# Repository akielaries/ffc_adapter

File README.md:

# FFC adapter board
This is a custom PCB to interface the FFC pins of the Tang Mega 138k and Tang Mega 60k FPGAs

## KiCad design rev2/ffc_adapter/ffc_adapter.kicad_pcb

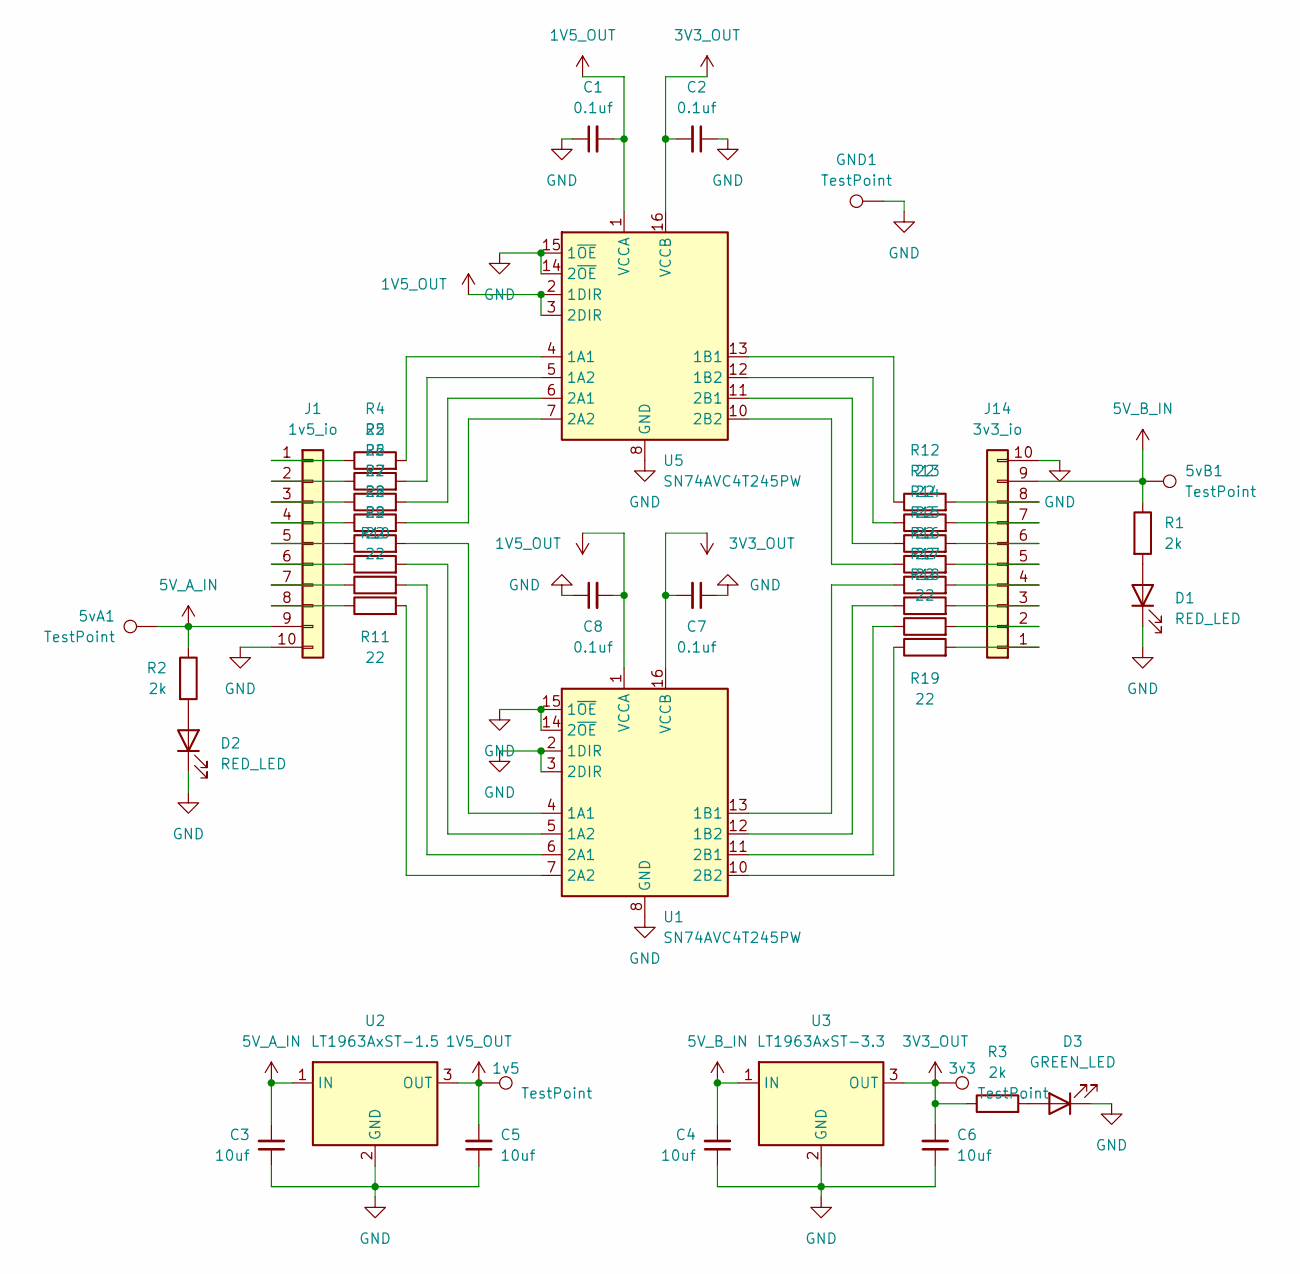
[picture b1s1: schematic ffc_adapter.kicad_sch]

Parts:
1v5, 3v3, 5vA1, 5vB1: TestPoint; TestPoint_Pad_D1.0mm
C1, C2, C7, C8: 0.1uf; C_0805_2012Metric
C3, C4, C5, C6: 10uf; C_0805_2012Metric
D1, D2: RED_LED; LED_0603_1608Metric
D3: GREEN_LED; LED_0603_1608Metric
GND1: TestPoint; TestPoint_Pad_D1.0mm
J1: 1v5_io; Hirose_FH12-10S-0.5SH_1x10-1MP_P0.50mm_Horizontal
J14: 3v3_io; Hirose_FH12-10S-0.5SH_1x10-1MP_P0.50mm_Horizontal
R1, R2, R3: 2k; R_0201_0603Metric; DigiKey_Part_Number 311-10.0KCRCT-ND
R4, R5, R6, R7, R8, R9, R10, R11, R12, R13, R14, R15, R16, R17, R18, R19: 22; R_0201_0603Metric; DigiKey_Part_Number 311-10.0KCRCT-ND
U1, U5: SN74AVC4T245PW; TSSOP-16_4.4x5mm_P0.65mm
U2: LT1963AxST-1.5; SOT-223-3_TabPin2
U3: LT1963AxST-3.3; SOT-223-3_TabPin2

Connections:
1V5_OUT: 1v5.1, C1.2, C5.2, C8.2, U1.1 (VCCA), U2.3 (OUT), U5.1 (VCCA), U5.2 (1DIR), U5.3 (2DIR)
3V3_OUT: 3v3.1, C2.2, C6.2, C7.2, R3.1, U1.16 (VCCB), U3.3 (OUT), U5.16 (VCCB)
5V_A_IN: 5vA1.1, C3.2, J1.9, R2.1, U2.1 (IN)
5V_B_IN: 5vB1.1, C4.2, J14.9, R1.1, U3.1 (IN)
GND: C1.1, C2.1, C3.1, C4.1, C5.1, C6.1, C7.1, C8.1, D1.1 (K), D2.1 (K), D3.1 (K), GND1.1, J1.10, J14.10, U1.2 (1DIR), U1.3 (2DIR), U1.8 (GND), U1.9 (GND), U1.14 (2~OE), U1.15 (1~OE), U2.2 (GND), U3.2 (GND), U5.8 (GND), U5.9 (GND), U5.14 (2~OE), U5.15 (1~OE)
unnamed: D1.2 (A), R1.2
unnamed: D2.2 (A), R2.2
unnamed: D3.2 (A), R3.2
unnamed: J1.1, R4.1
unnamed: J1.2, R5.1
unnamed: J1.3, R6.1
unnamed: J1.4, R7.1
unnamed: J1.5, R8.1
unnamed: J1.6, R9.1
unnamed: J1.7, R10.1
unnamed: J1.8, R11.1
unnamed: J14.1, R19.2
unnamed: J14.2, R18.2
unnamed: J14.3, R17.2
unnamed: J14.4, R16.2
unnamed: J14.5, R15.2
unnamed: J14.6, R14.2
unnamed: J14.7, R13.2
unnamed: J14.8, R12.2
unnamed: R8.2, U1.4 (1A1)
unnamed: R9.2, U1.5 (1A2)
unnamed: R16.1, U1.13 (1B1)
unnamed: R17.1, U1.12 (1B2)
unnamed: R10.2, U1.6 (2A1)
unnamed: R11.2, U1.7 (2A2)
unnamed: R18.1, U1.11 (2B1)
unnamed: R19.1, U1.10 (2B2)
unnamed: R4.2, U5.4 (1A1)
unnamed: R5.2, U5.5 (1A2)
unnamed: R12.1, U5.13 (1B1)
unnamed: R13.1, U5.12 (1B2)
unnamed: R6.2, U5.6 (2A1)
unnamed: R7.2, U5.7 (2A2)
unnamed: R14.1, U5.11 (2B1)
unnamed: R15.1, U5.10 (2B2)

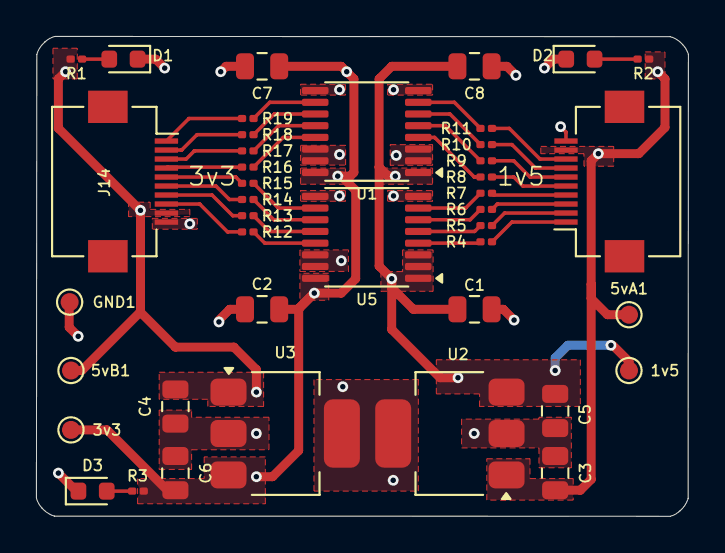
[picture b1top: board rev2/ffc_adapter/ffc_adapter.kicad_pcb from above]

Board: 2 copper layers, 36.2 x 26.7 mm, 41 parts (0 on the bottom side), 40 nets.

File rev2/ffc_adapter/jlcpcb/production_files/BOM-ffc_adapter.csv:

Comment,Designator,Footprint,LCSC,Quantity
10uf,C4,C_0805_2012Metric,,1
SN74AVC4T245PW,U1,TSSOP-16_4.4x5mm_P0.65mm,,1
GREEN_LED,D3,LED_0603_1608Metric,,1
10uf,C5,C_0805_2012Metric,,1
RED_LED,D1,LED_0603_1608Metric,,1
LT1963AxST-3.3,U3,SOT-223-3_TabPin2,,1
RED_LED,D2,LED_0603_1608Metric,,1
10uf,C6,C_0805_2012Metric,,1
LT1963AxST-1.5,U2,SOT-223-3_TabPin2,,1
2k,R3,R_0201_0603Metric,,1
22,R4,R_0201_0603Metric,,1
2k,R2,R_0201_0603Metric,,1
0.1uf,C2,C_0805_2012Metric,,1
10uf,C3,C_0805_2012Metric,,1
2k,R1,R_0201_0603Metric,,1
3v3_io,J14,Hirose_FH12-10S-0.5SH_1x10-1MP_P0.50mm_Horizontal,,1
0.1uf,C1,C_0805_2012Metric,,1
1v5_io,J1,Hirose_FH12-10S-0.5SH_1x10-1MP_P0.50mm_Horizontal,,1
TestPoint,3v3,TestPoint_Pad_D1.0mm,,1
TestPoint,1v5,TestPoint_Pad_D1.0mm,,1
22,R9,R_0201_0603Metric,,1
22,R17,R_0201_0603Metric,,1
22,R12,R_0201_0603Metric,,1
22,R16,R_0201_0603Metric,,1
22,R5,R_0201_0603Metric,,1
22,R8,R_0201_0603Metric,,1
22,R10,R_0201_0603Metric,,1
22,R14,R_0201_0603Metric,,1
22,R13,R_0201_0603Metric,,1
22,R6,R_0201_0603Metric,,1
TestPoint,GND1,TestPoint_Pad_D1.0mm,,1
0.1uf,C8,C_0805_2012Metric,,1
TestPoint,5vA1,TestPoint_Pad_D1.0mm,,1
22,R7,R_0201_0603Metric,,1
0.1uf,C7,C_0805_2012Metric,,1
TestPoint,5vB1,TestPoint_Pad_D1.0mm,,1
22,R11,R_0201_0603Metric,,1
22,R18,R_0201_0603Metric,,1
22,R19,R_0201_0603Metric,,1
SN74AVC4T245PW,U5,TSSOP-16_4.4x5mm_P0.65mm,,1
22,R15,R_0201_0603Metric,,1

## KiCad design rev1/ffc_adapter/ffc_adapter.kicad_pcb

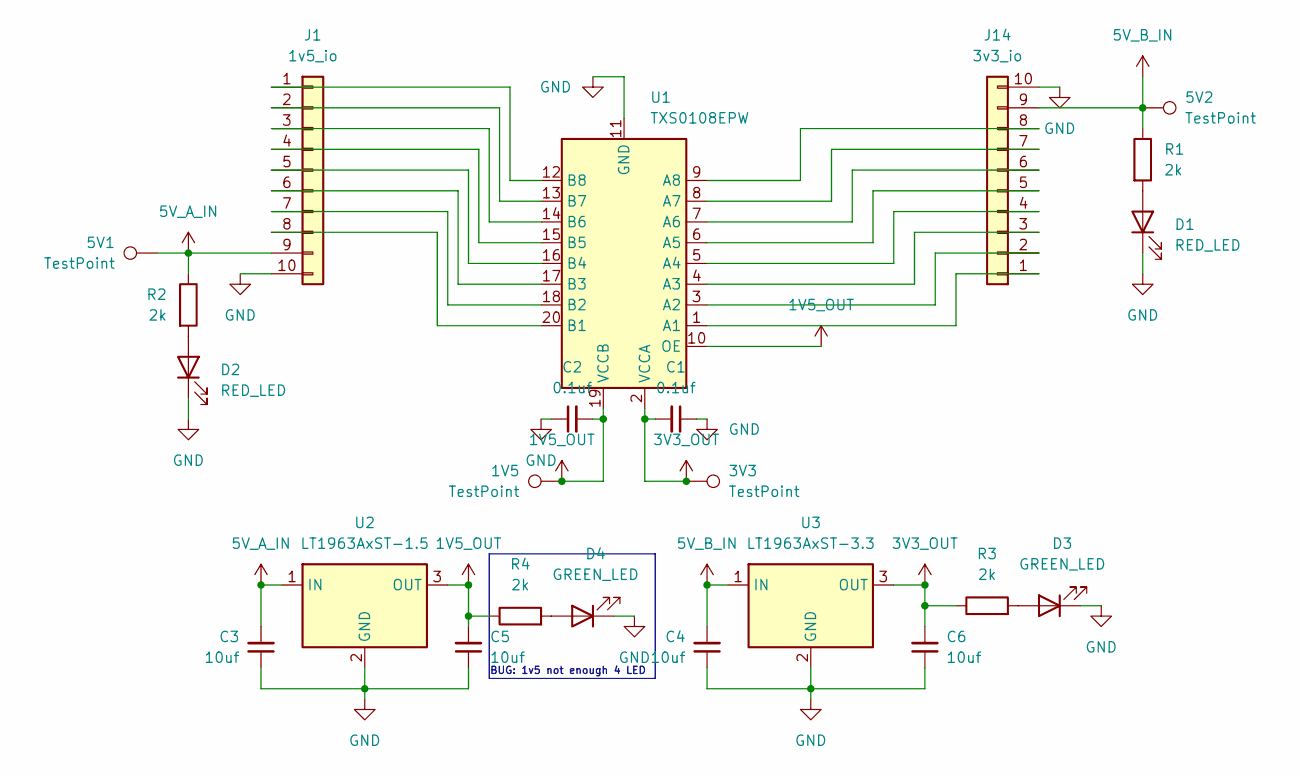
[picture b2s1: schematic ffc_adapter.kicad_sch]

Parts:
1V5, 3V3, 5V1, 5V2: TestPoint; TestPoint_Pad_D1.0mm
C1, C2: 0.1uf; C_0805_2012Metric
C3, C4, C5, C6: 10uf; C_0805_2012Metric
D1, D2: RED_LED; LED_0603_1608Metric
D3, D4: GREEN_LED; LED_0603_1608Metric
J1: 1v5_io; Hirose_FH12-10S-0.5SH_1x10-1MP_P0.50mm_Horizontal
J14: 3v3_io; Hirose_FH12-10S-0.5SH_1x10-1MP_P0.50mm_Horizontal
R1, R2, R3, R4: 2k; R_0805_2012Metric_Pad1.20x1.40mm_HandSolder; DigiKey_Part_Number 311-10.0KCRCT-ND
U1: TXS0108EPW; TSSOP-20_4.4x6.5mm_P0.65mm
U2: LT1963AxST-1.5; SOT-223-3_TabPin2
U3: LT1963AxST-3.3; SOT-223-3_TabPin2

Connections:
1V5_OUT: 1V5.1, C2.2, C5.2, R4.1, U1.10 (OE), U1.19 (VCCB), U2.3 (OUT)
3V3_OUT: 3V3.1, C1.2, C6.2, R3.1, U1.2 (VCCA), U3.3 (OUT)
5V_A_IN: 5V1.1, C3.2, J1.9, R2.1, U2.1 (IN)
5V_B_IN: 5V2.1, C4.2, J14.9, R1.1, U3.1 (IN)
GND: C1.1, C2.1, C3.1, C4.1, C5.1, C6.1, D1.1 (K), D2.1 (K), D3.1 (K), D4.1 (K), J1.10, J14.10, U1.11 (GND), U2.2 (GND), U3.2 (GND)
unnamed: D1.2 (A), R1.2
unnamed: D2.2 (A), R2.2
unnamed: D3.2 (A), R3.2
unnamed: D4.2 (A), R4.2
unnamed: J1.1, U1.12 (B8)
unnamed: J1.2, U1.13 (B7)
unnamed: J1.3, U1.14 (B6)
unnamed: J1.4, U1.15 (B5)
unnamed: J1.5, U1.16 (B4)
unnamed: J1.6, U1.17 (B3)
unnamed: J1.7, U1.18 (B2)
unnamed: J1.8, U1.20 (B1)
unnamed: J14.1, U1.1 (A1)
unnamed: J14.2, U1.3 (A2)
unnamed: J14.3, U1.4 (A3)
unnamed: J14.4, U1.5 (A4)
unnamed: J14.5, U1.6 (A5)
unnamed: J14.6, U1.7 (A6)
unnamed: J14.7, U1.8 (A7)
unnamed: J14.8, U1.9 (A8)

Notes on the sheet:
BUG: 1v5 not enough 4 LED

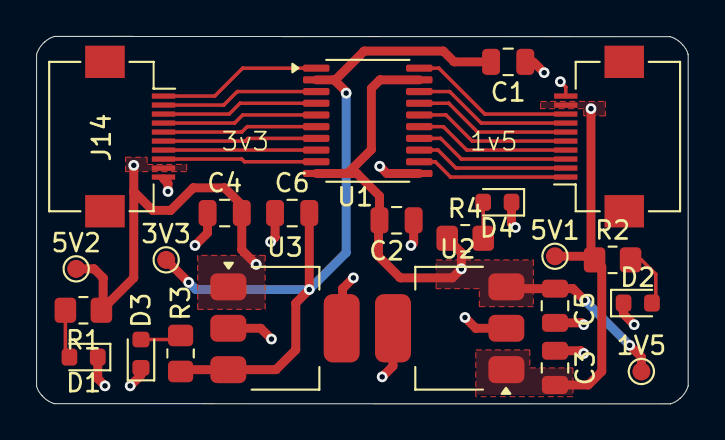
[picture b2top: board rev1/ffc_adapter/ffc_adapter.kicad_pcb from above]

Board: 2 copper layers, 36.2 x 20.4 mm, 23 parts (0 on the bottom side), 25 nets.

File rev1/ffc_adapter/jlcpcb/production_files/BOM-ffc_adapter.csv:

Comment,Designator,Footprint,LCSC,Quantity
10uf,C4,C_0805_2012Metric,,1
TXS0108EPW,U1,TSSOP-20_4.4x6.5mm_P0.65mm,,1
LED,D3,LED_0603_1608Metric,,1
LED,D4,LED_0603_1608Metric,,1
10uf,C5,C_0805_2012Metric,,1
LED,D1,LED_0603_1608Metric,,1
LT1963AxST-3.3,U3,SOT-223-3_TabPin2,,1
LED,D2,LED_0603_1608Metric,,1
10uf,C6,C_0805_2012Metric,,1
LT1963AxST-1.5,U2,SOT-223-3_TabPin2,,1
2k,R3,R_0805_2012Metric_Pad1.20x1.40mm_HandSolder,,1
2k,R4,R_0805_2012Metric_Pad1.20x1.40mm_HandSolder,,1
2k,R2,R_0805_2012Metric_Pad1.20x1.40mm_HandSolder,,1
0.1uf,C2,C_0805_2012Metric,,1
10uf,C3,C_0805_2012Metric,,1
2k,R1,R_0805_2012Metric_Pad1.20x1.40mm_HandSolder,,1
3v3_io,J14,Hirose_FH12-10S-0.5SH_1x10-1MP_P0.50mm_Horizontal,,1
0.1uf,C1,C_0805_2012Metric,,1
1v5_io,J1,Hirose_FH12-10S-0.5SH_1x10-1MP_P0.50mm_Horizontal,,1
TestPoint,5V2,TestPoint_Pad_D1.0mm,,1
TestPoint,3V3,TestPoint_Pad_D1.0mm,,1
TestPoint,1V5,TestPoint_Pad_D1.0mm,,1
TestPoint,5V1,TestPoint_Pad_D1.0mm,,1

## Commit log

2026-03-29 add things
2026-04-25 sent rev 2 to jlcpcb
